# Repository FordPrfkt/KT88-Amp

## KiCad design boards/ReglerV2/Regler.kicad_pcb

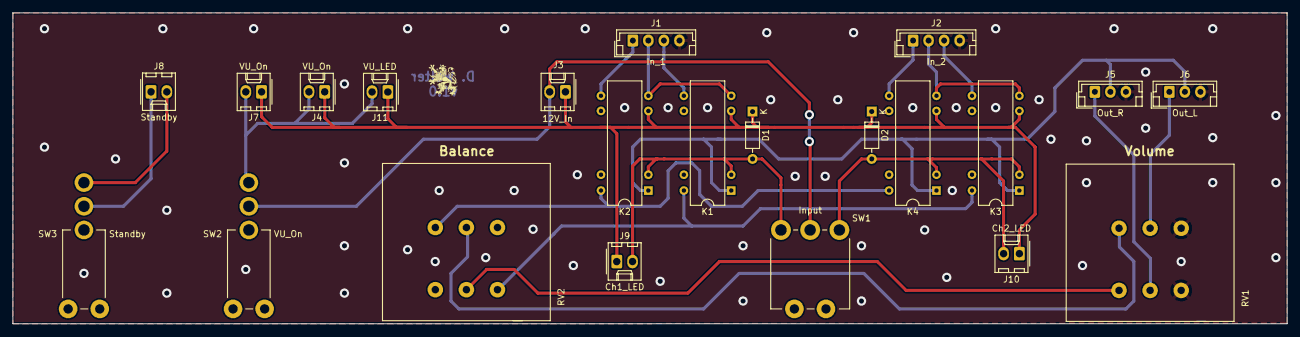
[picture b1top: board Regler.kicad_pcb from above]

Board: 2 copper layers, 205.0 x 50.0 mm, 22 parts (0 on the bottom side), 21 nets.

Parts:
D1, D2: 1N4148; D_DO-35_SOD27_P7.62mm_Horizontal
J1: In_1; JST_EH_B4B-EH-A_1x04_P2.50mm_Vertical
J2: In_2; JST_EH_B4B-EH-A_1x04_P2.50mm_Vertical
J3: 12V_In; Molex_KK-254_AE-6410-02A_1x02_P2.54mm_Vertical
J4, J7: VU_On; Molex_KK-254_AE-6410-02A_1x02_P2.54mm_Vertical
J5: Out_R; JST_EH_B3B-EH-A_1x03_P2.50mm_Vertical
J6: Out_L; JST_EH_B3B-EH-A_1x03_P2.50mm_Vertical
J8: Standby; Molex_KK-254_AE-6410-02A_1x02_P2.54mm_Vertical
J9: Ch1_LED; Molex_KK-254_AE-6410-02A_1x02_P2.54mm_Vertical
J10: Ch2_LED; Molex_KK-254_AE-6410-02A_1x02_P2.54mm_Vertical
J11: VU_LED; Molex_KK-254_AE-6410-02A_1x02_P2.54mm_Vertical
K1, K2, K3, K4: DIPxx-2Axx-21x; Relay_StandexMeder_DIP_LowProfile
RV1: Alps 20k log; Potentiometer_Alps-RK271-double
RV2: Alps 50k lin; Potentiometer_Alps-RK271-double
SW1: Input; 7101MD9ABE
SW2: VU_On; 7101MD9AV2BE
SW3: Standby; 7101MD9AV2BE

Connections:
+12V: D1.1 (K), D2.1 (K), J3.1, J4.1, J7.1, J9.1, J10.1, J11.1, K1.6, K2.6, K3.6, K4.6
/CH_1: D1.2 (A), J9.2, K1.2, K2.2, SW1.3 (C)
/CH_2: D2.2 (A), J10.2, K3.2, K4.2, SW1.1 (A)
/GND_1: J1.2, K1.7, K2.7
/GND_2: J2.2, K3.7, K4.7
/L_1: J1.1, K2.8
/L_2: J2.1, K4.8
/L_Out: J6.1, RV1.5
/L_Sw: K2.14, K4.14, RV2.4
/R_1: J1.3, K1.8
/R_2: J2.3, K3.8
/R_Out: J5.1, RV1.2
/R_Sw: K1.14, K3.14, RV2.3
Earth_Clean: J1.4, J2.4, J5.3, J6.3, RV1.3, RV1.6
GND: J3.2, SW1.2 (B), SW2.2 (B)
GNDS: J5.2, J6.2, K1.1, K2.1, K3.1, K4.1
unnamed: J8.1, SW3.2 (B)
unnamed: J8.2, SW3.3 (C)
unnamed: J4.2, J7.2, J11.2, SW2.3 (C)
unnamed: RV1.1, RV2.2
unnamed: RV1.4, RV2.5
